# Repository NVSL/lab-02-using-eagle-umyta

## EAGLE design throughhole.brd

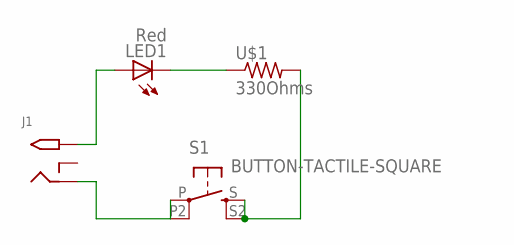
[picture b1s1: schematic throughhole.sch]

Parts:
J1: 2.1MMJACKTHM; PJ-102A
LED1: Red; LED5MM
S1: BUTTON-TACTILE-SQUARE; BUTTON-TACTILE-SQUARE-ADAFRUIT1010
U$1: 330Ohms; RESAD1160W55L680D260_HS

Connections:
unnamed: J1.RING, S1.P, S1.P2 (P1)
unnamed: LED1.K (C), U$1.1
unnamed: S1.S, S1.S2 (S1), U$1.2
unnamed: J1.TIP, LED1.A

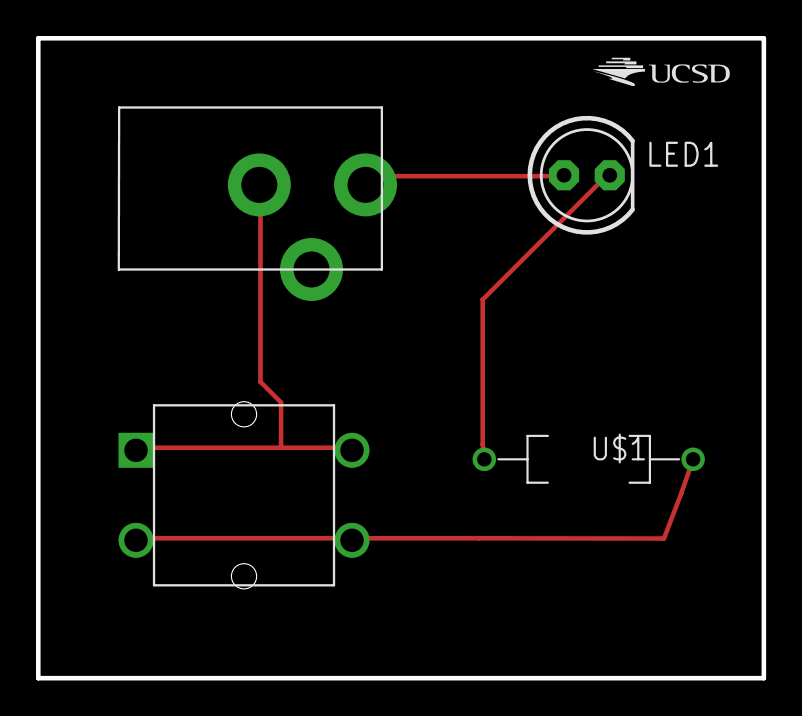
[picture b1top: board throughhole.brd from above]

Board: 2 copper layers, 40.3 x 35.5 mm, 5 parts (0 on the bottom side), 4 nets.

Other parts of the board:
U$2: UCSD_LOGO

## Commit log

2016-04-07 Finished throughhole part
2016-04-07 First attempt with the library
2016-04-07 added smd board and schema
2016-04-07 Added smd cam file.
2016-04-07 added updated sainan-Lab2.lbr
2016-04-07 ran check.
2016-04-07 Added logo to the boards.
2016-04-07 First report
2016-04-07 Add SMD report, which arrived 5am in the early morning.
